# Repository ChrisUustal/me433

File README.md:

# ME433 - Advanced Mechatronics
### Chris Uustal | Northwestern University | Spring '22

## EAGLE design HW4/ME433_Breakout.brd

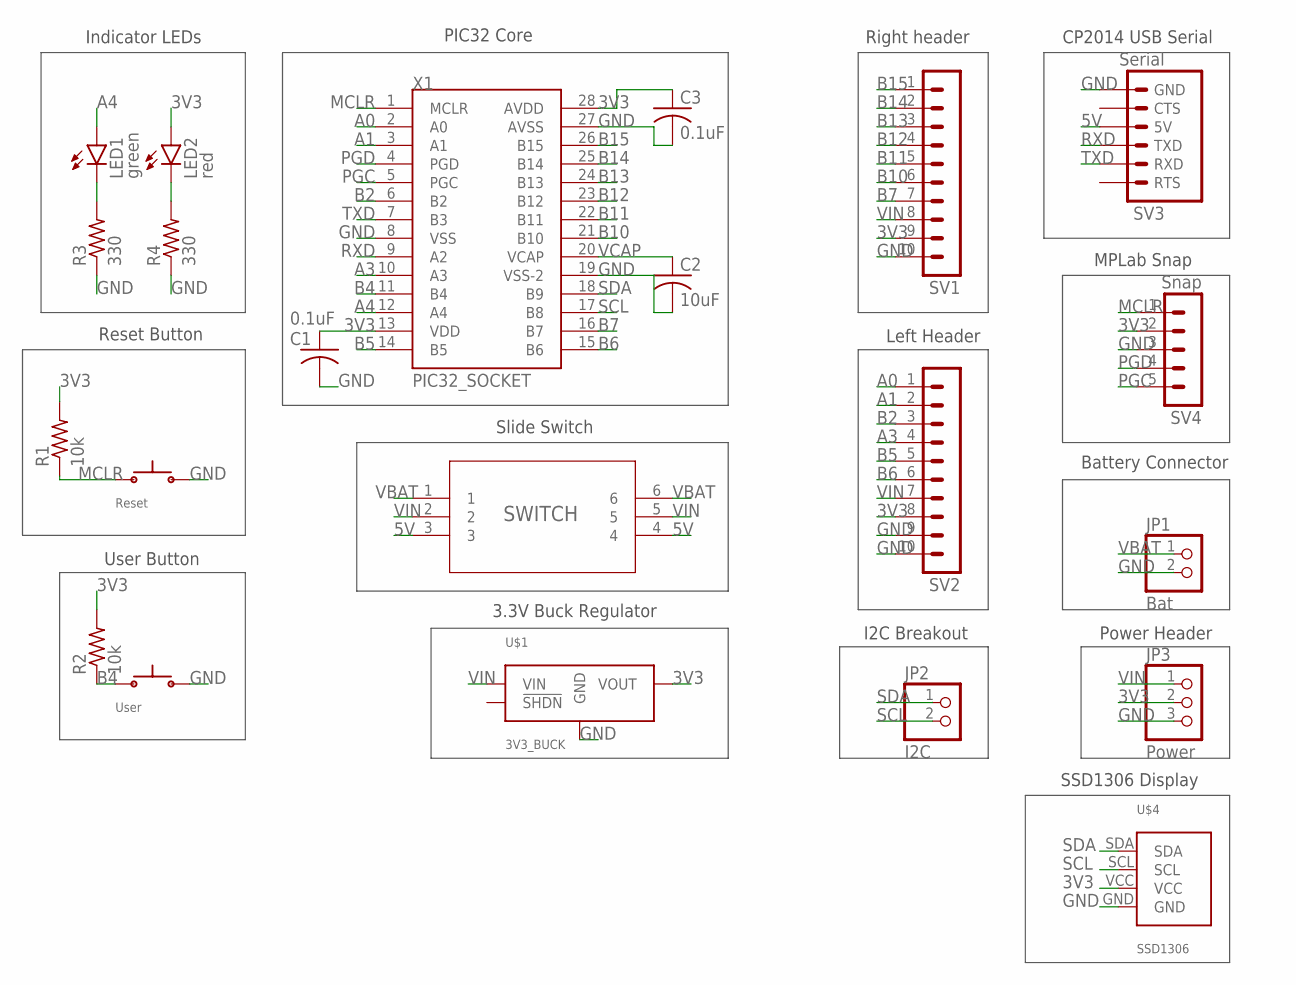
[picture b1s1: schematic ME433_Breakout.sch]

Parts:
C1, C3: 0.1uF; C025-025X050
C2: 10uF; C025-025X050
JP1: Bat; 1X02
JP2: I2C; 1X02
JP3: Power; 1X03
LED1: green; LED3MM
LED2: red; LED3MM
R1, R2: 10k; 0207/10
R3, R4: 330; 0207/10
SV1, SV2: MA10-1
SV3: Serial; MA06-1
SV4: Snap; MA05-1
U1: SWITCH; SWITCH_011CQN
U$1: 3V3_BUCK
U$2: Reset; PUSH_BUTTON
U$3: User; PUSH_BUTTON
U$4: SSD1306
X1: PIC32_SOCKET; OST_ED281DT

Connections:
3V3: C1.1, C3.1, JP3.2, LED2.A, R1.2, R2.2, SV1.9, SV2.8, SV4.2, U$1.VOUT, U$4.VCC, X1.13 (VDD), X1.28 (AVDD)
5V: SV3.5V, U1.3, U1.4
A0: SV2.1, X1.2 (A0)
A1: SV2.2, X1.3 (A1)
A3: SV2.4, X1.10 (A3)
A4: LED1.A, X1.12 (A4)
B2: SV2.3, X1.6 (B2)
B4: R2.1, U$3.P$1, X1.11 (B4)
B5: SV2.5, X1.14 (B5)
B6: SV2.6, X1.15 (B6)
B7: SV1.7, X1.16 (B7)
B10: SV1.6, X1.21 (B10)
B11: SV1.5, X1.22 (B11)
B12: SV1.4, X1.23 (B12)
B13: SV1.3, X1.24 (B13)
B14: SV1.2, X1.25 (B14)
B15: SV1.1, X1.26 (B15)
GND: C1.2, C2.2, C3.2, JP1.2, JP3.3, R3.1, R4.1, SV1.10, SV2.9, SV2.10, SV3.GND, SV4.3, U$1.GND, U$2.P$2, U$3.P$2, U$4.GND, X1.8 (VSS), X1.19 (VSS-2), X1.27 (AVSS)
MCLR: R1.1, SV4.1, U$2.P$1, X1.1 (MCLR)
unnamed: LED1.K (C), R3.2
unnamed: LED2.K (C), R4.2
PGC: SV4.5, X1.5 (PGC)
PGD: SV4.4, X1.4 (PGD)
RXD: SV3.TXD, X1.9 (A2)
SCL: JP2.2, U$4.SCL, X1.17 (B8)
SDA: JP2.1, U$4.SDA, X1.18 (B9)
TXD: SV3.RXD, X1.7 (B3)
VBAT: JP1.1, U1.1, U1.6
VCAP: C2.1, X1.20 (VCAP)
VIN: JP3.1, SV1.8, SV2.7, U1.2, U1.5, U$1.VIN

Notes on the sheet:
Right header
Left Header
3.3V Buck Regulator
CP2014 USB Serial
MPLab Snap
Battery Connector
Reset Button
User Button
Slide Switch
I2C Breakout
Indicator LEDs
Power Header
PIC32 Core
SSD1306 Display

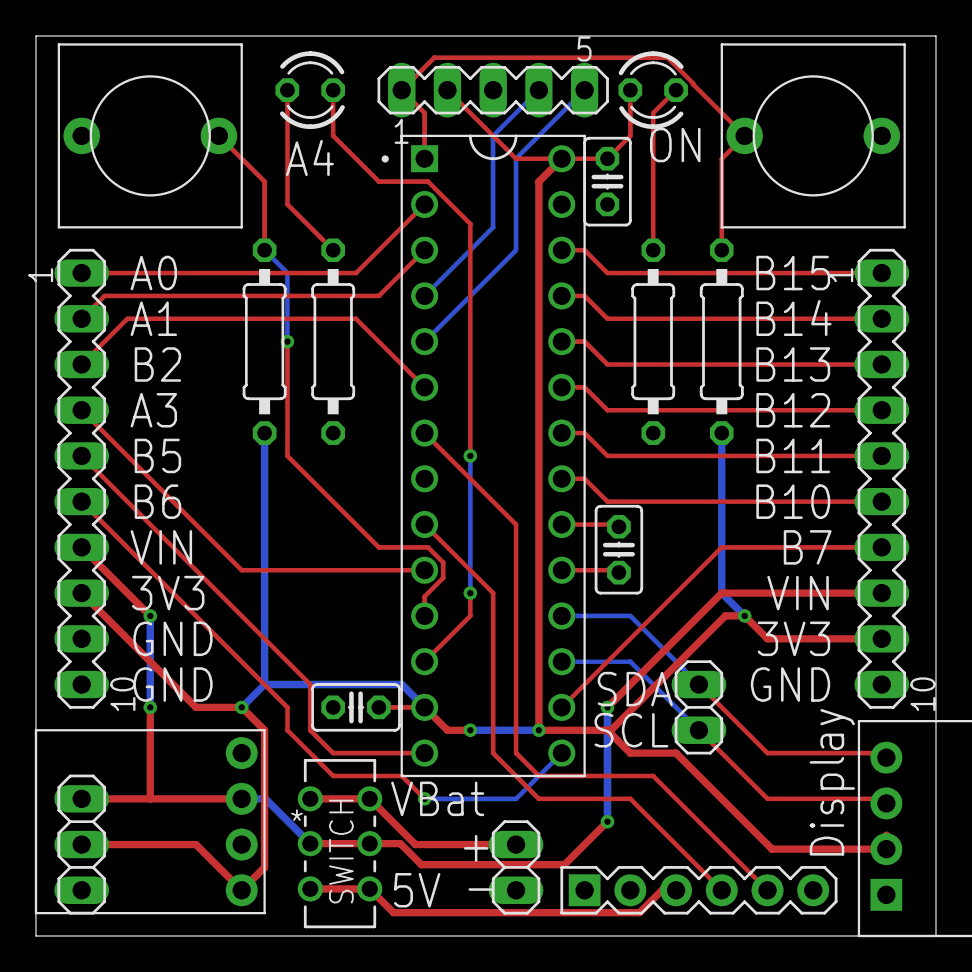
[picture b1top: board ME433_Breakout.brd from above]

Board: 2 copper layers, 50.0 x 50.0 mm, 22 parts (0 on the bottom side), 30 nets.

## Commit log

2022-03-24 added test file
2022-04-04 hw2 started
2022-04-04 moved code
2022-04-04 circuit diagram + pic
2022-04-04 finished hw2
2022-04-05 added hw3 directory
2022-04-05 finished hw3
2022-04-12 added gerber
2022-05-17 hw10
2022-05-17 hw11

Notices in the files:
parts and their libraries:
COPYRIGHT: Copyright (C) 2022 Ultra Librarian. All rights reserved.
